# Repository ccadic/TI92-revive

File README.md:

# TI92-revive
Reviing the TI92 calculator with a new KICAD PCB and a new 4 inch display

This project is still experimental. We need you help !!!!

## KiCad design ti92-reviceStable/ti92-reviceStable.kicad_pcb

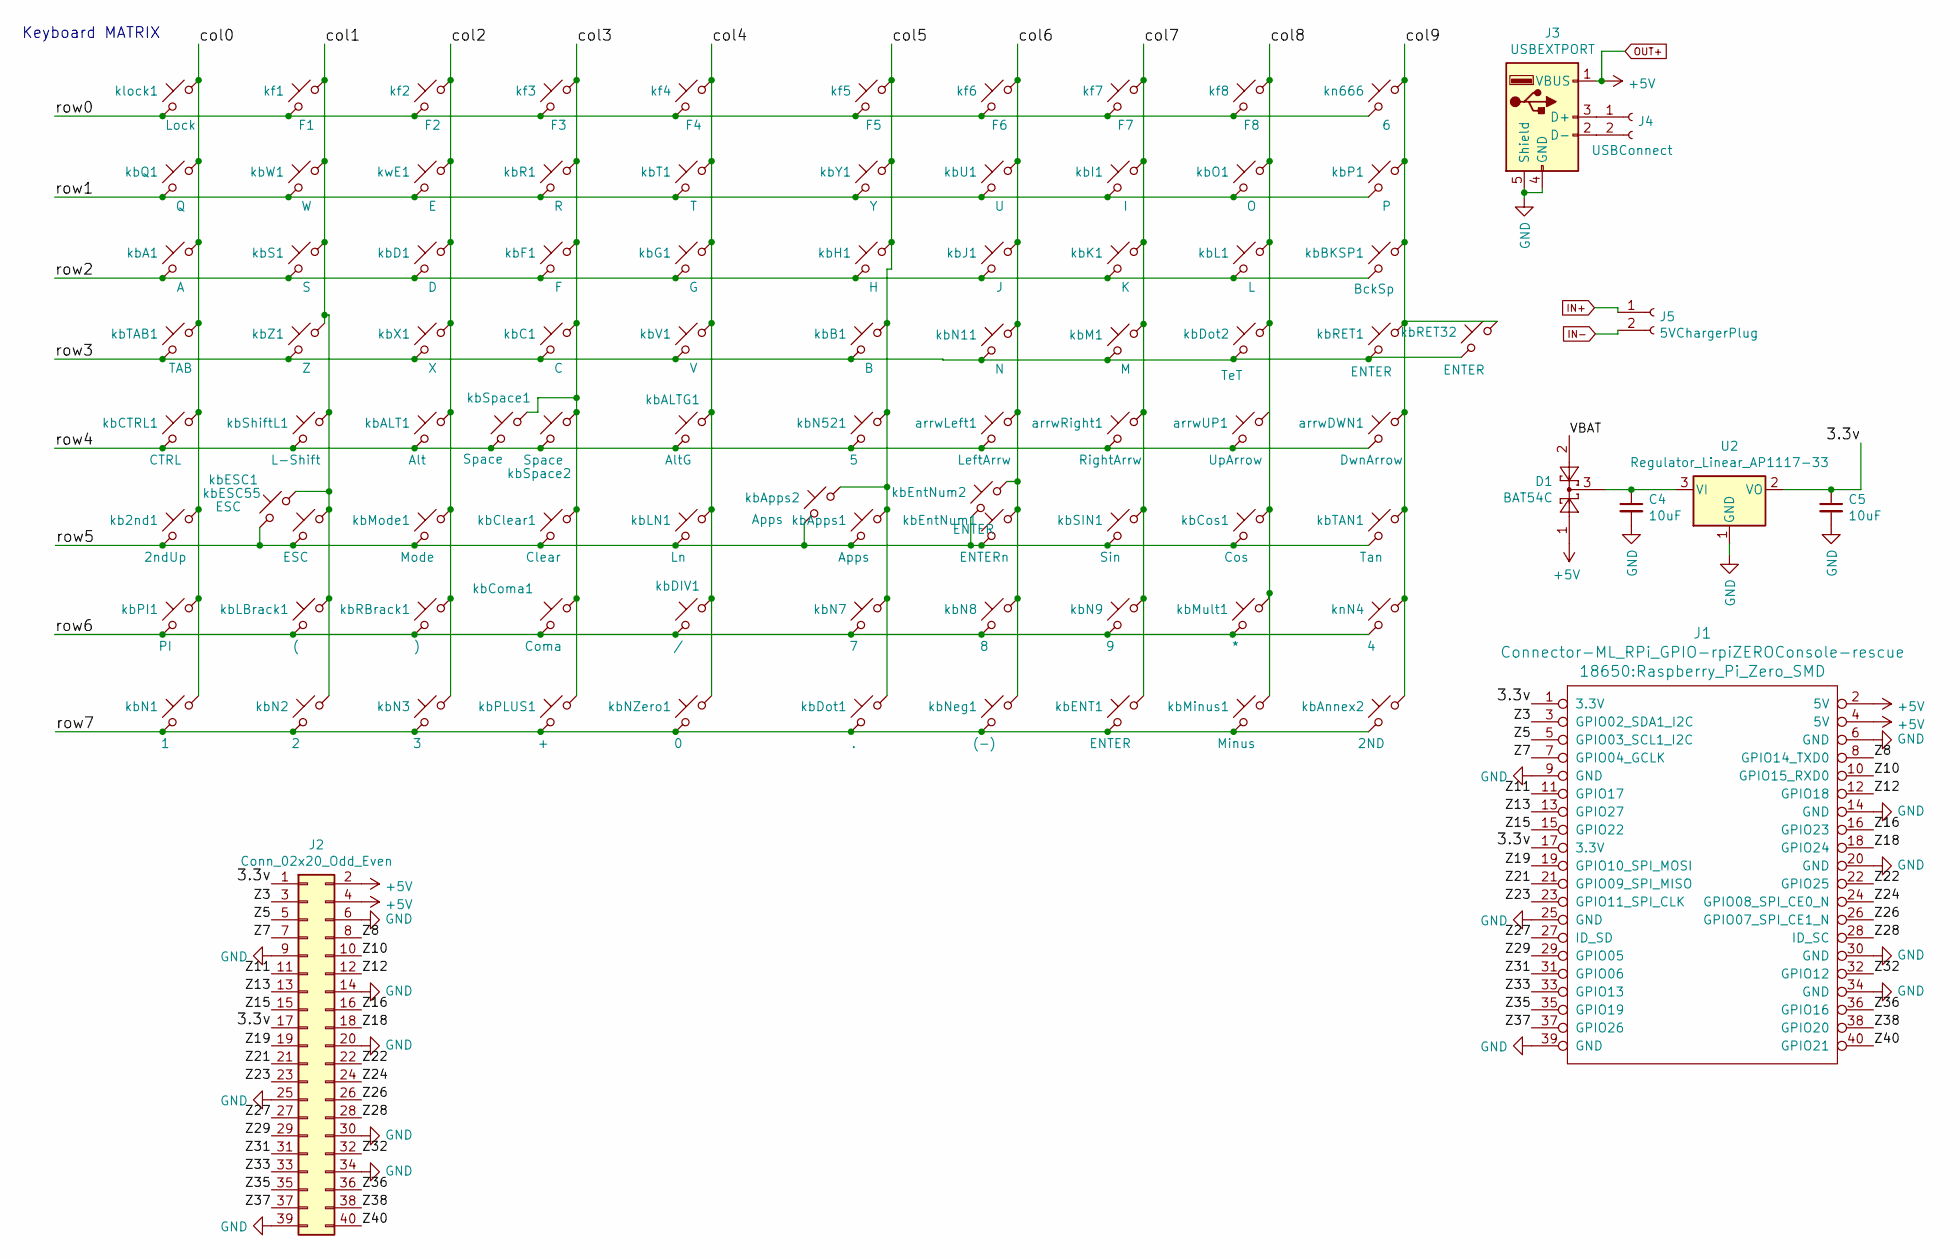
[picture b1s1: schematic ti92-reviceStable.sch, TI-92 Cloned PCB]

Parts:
C4, C5: 10uF; C_0805_2012Metric_Pad1.18x1.45mm_HandSolder
D1: BAT54C; SOT-23
J1: Connector-ML_RPi_GPIO-rpiZEROConsole-rescue; Raspberry_Pi_Zero_SMD
J2: Conn_02x20_Odd_Even; 4inchIPSDisplay
J3: USBEXTPORT; usbAsmd
J4: USBConnect; 2pads
J5: 5VChargerPlug; BARREL_JACK
U2: Regulator_Linear_AP1117-33; SOT-223-3_TabPin2
arrwDWN1: DwnArrow; Kpad6
arrwLeft1: LeftArrw; Kpad6
arrwRight1: RightArrw; Kpad6
arrwUP1: UpArrow; Kpad6
kb2nd1: 2ndUp; Kpad6
kbA1: A; Kpad6
kbALT1: Alt; Kpad6
kbALTG1: AltG; Kpad6
kbAnnex2: 2ND; Kpad6
kbApps1, kbApps2: Apps; Kpad6
kbB1: B; Kpad6
kbBKSP1: BckSp; Kpad6
kbC1: C; Kpad6
kbCTRL1: CTRL; Kpad6
kbClear1: Clear; Kpad6
kbComa1: Coma; Kpad6
kbCos1: Cos; Kpad6
kbD1: D; Kpad6
kbDIV1: /; Kpad6
kbDot1: .; Kpad6
kbDot2: TeT; Kpad6
kbENT1: ENTER; Kpad6
kbESC1, kbESC55: ESC; Kpad6
kbEntNum1: ENTERn; Kpad6
kbEntNum2: ENTER; Kpad6
kbF1: F; Kpad6
kbG1: G; Kpad6
kbH1: H; Kpad6
kbI1: I; Kpad6
kbJ1: J; Kpad6
kbK1: K; Kpad6
kbL1: L; Kpad6
kbLBrack1: (; Kpad6
kbLN1: Ln; Kpad6
kbM1: M; Kpad6
kbMinus1: Minus; Kpad6
kbMode1: Mode; Kpad6
kbMult1: *; Kpad6
kbN1: 1; Kpad6
kbN2: 2; Kpad6
kbN3: 3; Kpad6
kbN7: 7; Kpad6
kbN8: 8; Kpad6
kbN9: 9; Kpad6
kbN11: N; Kpad6
kbN521: 5; Kpad6
kbNZero1: 0; Kpad6
kbNeg1: (-); Kpad6
kbO1: O; Kpad6
kbP1: P; Kpad6
kbPI1: PI; Kpad6
kbPLUS1: +; Kpad6
kbQ1: Q; Kpad6
kbR1: R; Kpad6
kbRBrack1: ); Kpad6
kbRET1, kbRET32: ENTER; Kpad6
kbS1: S; Kpad6
kbSIN1: Sin; Kpad6
kbShiftL1: L-Shift; Kpad6
kbSpace1, kbSpace2: Space; Kpad6
kbT1: T; Kpad6
kbTAB1: TAB; Kpad6
kbTAN1: Tan; Kpad6
kbU1: U; Kpad6
kbV1: V; Kpad6
kbW1: W; Kpad6
kbX1: X; Kpad6
kbY1: Y; Kpad6
kbZ1: Z; Kpad6
kf1: F1; Kpad6
kf2: F2; Kpad6
kf3: F3; Kpad6
kf4: F4; Kpad6
kf5: F5; Kpad6
kf6: F6; Kpad6
kf7: F7; Kpad6
kf8: F8; Kpad6
klock1: Lock; Kpad6
kn666: 6; Kpad6
knN4: 4; Kpad6
kwE1: E; Kpad6

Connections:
/3.3v: C5.1, J1.1 (3.3V), J1.17 (3.3V), J2.1, J2.17, U2.2 (VO)
/VBAT: D1.2
/Z3: J1.3 (GPIO02_SDA1_I2C), J2.3
/Z5: J1.5 (GPIO03_SCL1_I2C), J2.5
/Z7: J1.7 (GPIO04_GCLK), J2.7
/Z8: J1.8 (GPIO14_TXD0), J2.8
/Z10: J1.10 (GPIO15_RXD0), J2.10
/Z11: J1.11 (GPIO17), J2.11
/Z12: J1.12 (GPIO18), J2.12
/Z13: J1.13 (GPIO27), J2.13
/Z15: J1.15 (GPIO22), J2.15
/Z16: J1.16 (GPIO23), J2.16
/Z18: J1.18 (GPIO24), J2.18
/Z19: J1.19 (GPIO10_SPI_MOSI), J2.19
/Z21: J1.21 (GPIO09_SPI_MISO), J2.21
/Z22: J1.22 (GPIO25), J2.22
/Z23: J1.23 (GPIO11_SPI_CLK), J2.23
/Z24: J1.24 (GPIO08_SPI_CE0_N), J2.24
/Z26: J1.26 (GPIO07_SPI_CE1_N), J2.26
/Z27: J1.27 (ID_SD), J2.27
/Z28: J1.28 (ID_SC), J2.28
/Z29: J1.29 (GPIO05), J2.29
/Z31: J1.31 (GPIO06), J2.31
/Z32: J1.32 (GPIO12), J2.32
/Z33: J1.33 (GPIO13), J2.33
/Z35: J1.35 (GPIO19), J2.35
/Z36: J1.36 (GPIO16), J2.36
/Z37: J1.37 (GPIO26), J2.37
/Z38: J1.38 (GPIO20), J2.38
/Z40: J1.40 (GPIO21), J2.40
/col0: kb2nd1.1, kbA1.1, kbCTRL1.1, kbN1.1, kbPI1.1, kbQ1.1, kbTAB1.1, klock1.1
/col1: kbESC1.1, kbESC55.1, kbLBrack1.1, kbN2.1, kbS1.1, kbShiftL1.1, kbW1.1, kbZ1.1, kf1.1
/col2: kbALT1.1, kbD1.1, kbMode1.1, kbN3.1, kbRBrack1.1, kbX1.1, kf2.1, kwE1.1
/col3: kbC1.1, kbClear1.1, kbComa1.1, kbF1.1, kbPLUS1.1, kbR1.1, kbSpace1.1, kbSpace2.1, kf3.1
/col4: kbALTG1.1, kbDIV1.1, kbG1.1, kbLN1.1, kbNZero1.1, kbT1.1, kbV1.1, kf4.1
/col5: kbApps1.1, kbApps2.1, kbB1.1, kbDot1.1, kbH1.1, kbN7.1, kbN521.1, kbY1.1, kf5.1
/col6: arrwLeft1.1, kbEntNum1.1, kbEntNum2.1, kbJ1.1, kbN8.1, kbN11.1, kbNeg1.1, kbU1.1, kf6.1
/col7: arrwRight1.1, kbENT1.1, kbI1.1, kbK1.1, kbM1.1, kbN9.1, kbSIN1.1, kf7.1
/col8: kbCos1.1, kbDot2.1, kbL1.1, kbMinus1.1, kbMult1.1, kbO1.1, kf8.1
/col9: arrwDWN1.1, kbAnnex2.1, kbBKSP1.1, kbP1.1, kbRET1.1, kbRET32.1, kbTAN1.1, kn666.1, knN4.1
/row0: kf1.2, kf2.2, kf3.2, kf4.2, kf5.2, kf6.2, kf7.2, kf8.2, klock1.2, kn666.2
/row1: kbI1.2, kbO1.2, kbP1.2, kbQ1.2, kbR1.2, kbT1.2, kbU1.2, kbW1.2, kbY1.2, kwE1.2
/row2: kbA1.2, kbBKSP1.2, kbD1.2, kbF1.2, kbG1.2, kbH1.2, kbJ1.2, kbK1.2, kbL1.2, kbS1.2
/row3: kbB1.2, kbC1.2, kbDot2.2, kbM1.2, kbN11.2, kbRET1.2, kbRET32.2, kbTAB1.2, kbV1.2, kbX1.2, kbZ1.2
/row4: arrwDWN1.2, arrwLeft1.2, arrwRight1.2, arrwUP1.2, kbALT1.2, kbALTG1.2, kbCTRL1.2, kbN521.2, kbShiftL1.2, kbSpace1.2, kbSpace2.2
/row5: kb2nd1.2, kbApps1.2, kbApps2.2, kbClear1.2, kbCos1.2, kbESC1.2, kbESC55.2, kbEntNum1.2, kbEntNum2.2, kbLN1.2, kbMode1.2, kbSIN1.2, kbTAN1.2
/row6: kbComa1.2, kbDIV1.2, kbLBrack1.2, kbMult1.2, kbN7.2, kbN8.2, kbN9.2, kbPI1.2, kbRBrack1.2, knN4.2
/row7: kbAnnex2.2, kbDot1.2, kbENT1.2, kbMinus1.2, kbN1.2, kbN2.2, kbN3.2, kbNZero1.2, kbNeg1.2, kbPLUS1.2
GND: C4.2, C5.2, J1.6 (GND), J1.9 (GND), J1.14 (GND), J1.20 (GND), J1.25 (GND), J1.30 (GND), J1.34 (GND), J1.39 (GND), J2.6, J2.9, J2.14, J2.20, J2.25, J2.30, J2.34, J2.39, J3.4 (GND), J3.5 (Shield), U2.1 (GND)
IN+: J5.1
IN-: J5.2
unnamed: C4.1, D1.3, U2.3 (VI)
unnamed: J3.2 (D-), J4.2
unnamed: J3.3 (D+), J4.1
OUT+: D1.1, J1.2 (5V), J1.4 (5V), J2.2, J2.4, J3.1 (VBUS)

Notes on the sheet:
Keyboard MATRIX

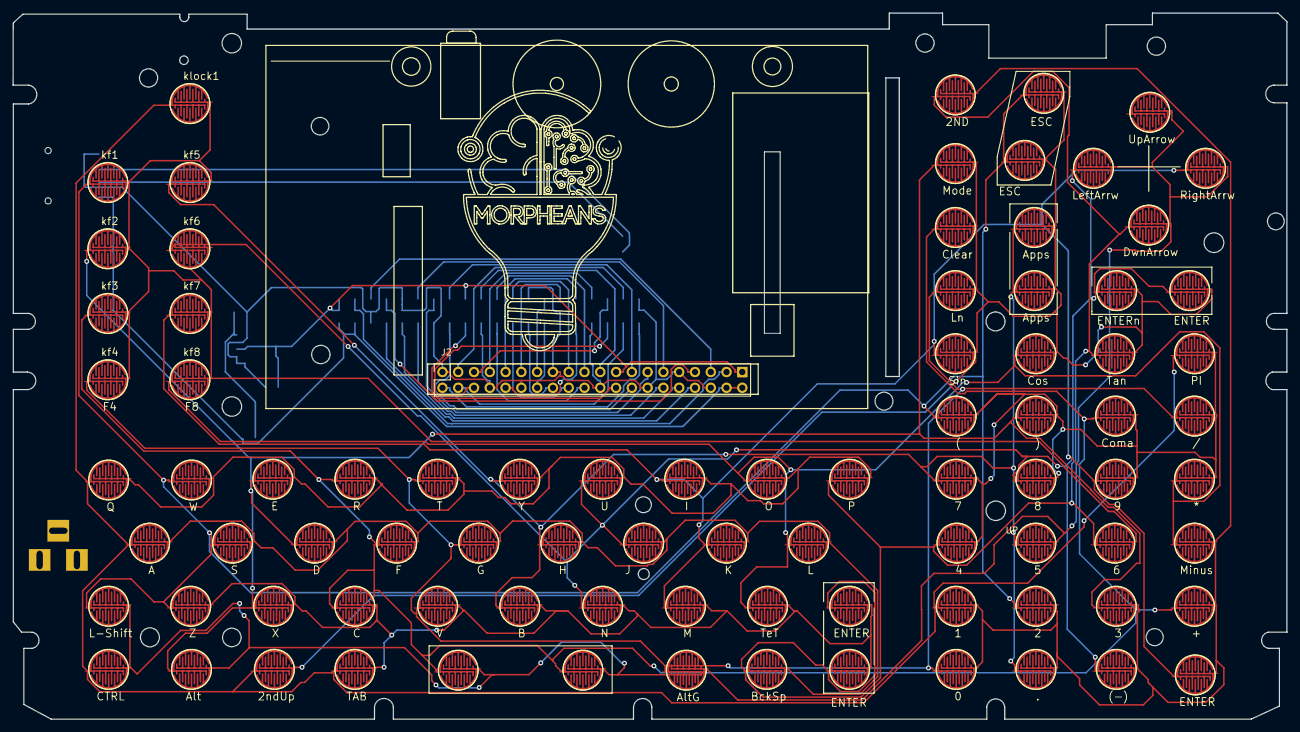
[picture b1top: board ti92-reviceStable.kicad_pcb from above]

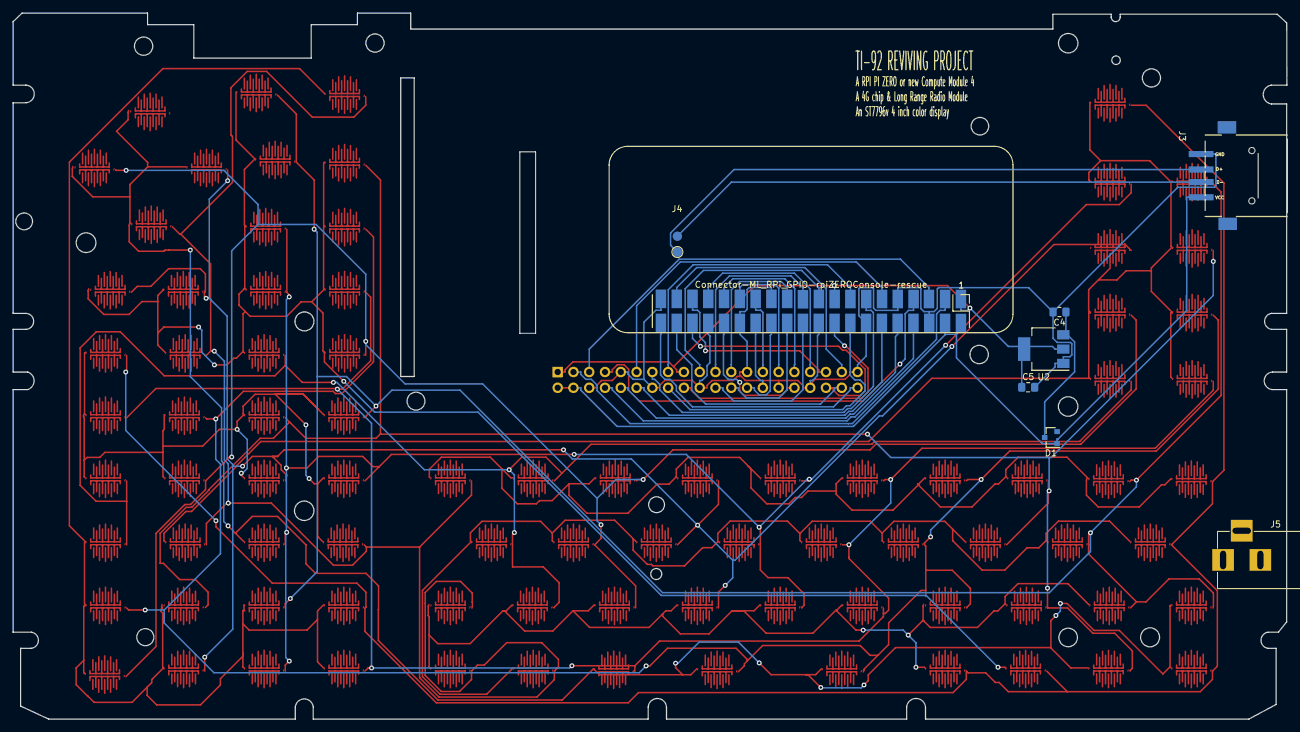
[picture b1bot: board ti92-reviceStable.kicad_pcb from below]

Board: 2 copper layers, 205.0 x 113.6 mm, 94 parts (8 on the bottom side), 52 nets.

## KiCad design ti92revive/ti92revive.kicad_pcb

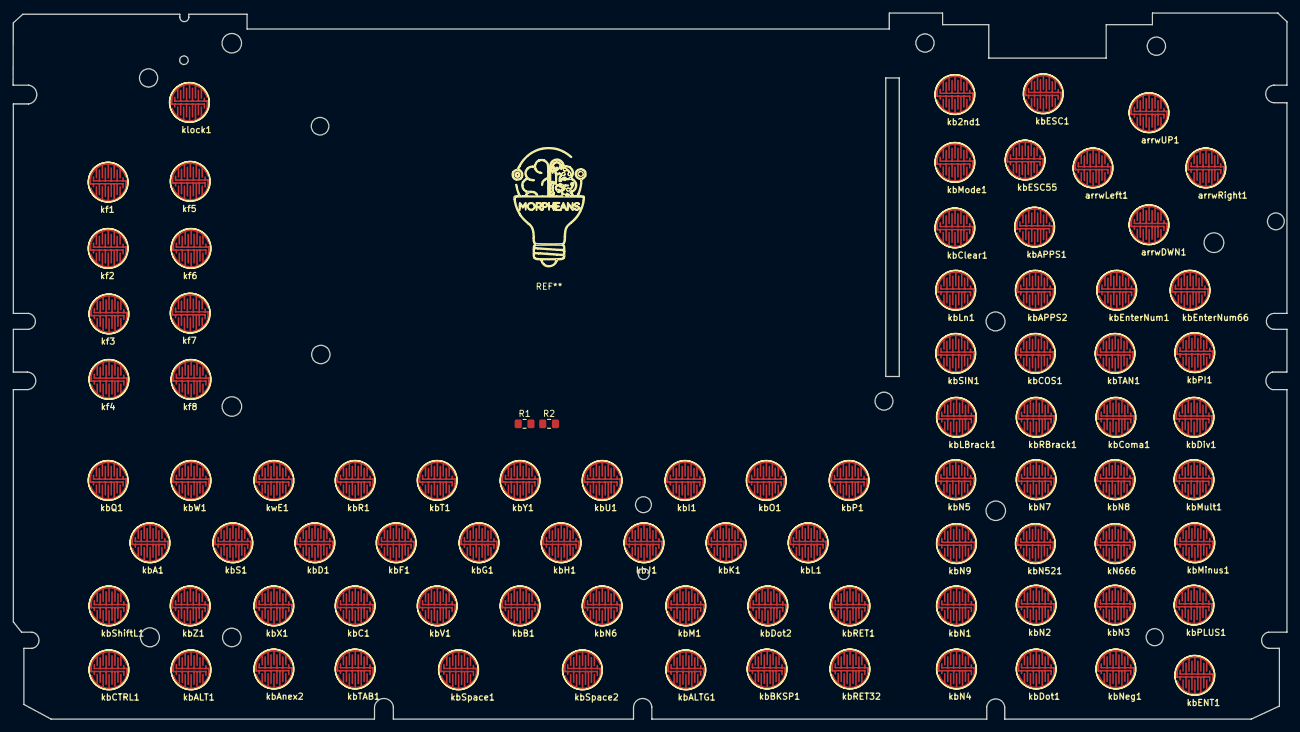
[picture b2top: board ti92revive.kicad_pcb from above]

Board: 2 copper layers, 205.0 x 113.6 mm, 88 parts (1 on the bottom side), 21 nets, no tracks yet.

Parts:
IC1: TCA8418; TCA8418-WQFN-24-1EP_4x4mm
R1: 4.7k; R_0805_2012Metric_Pad1.15x1.40mm_HandSolder
R2: 10k; R_0805_2012Metric_Pad1.15x1.40mm_HandSolder
arrwDWN1: ArwDwn; Kbpad
arrwLeft1: ArwLeft; Kbpad
arrwRight1: ArwRight; Kbpad
arrwUP1: ArwUP; Kbpad
kN666: 6; Kbpad
kb2nd1: 2ndUP; Kbpad
kbA1: A; Kbpad
kbALT1: Alt; Kbpad
kbALTG1: AltG; Kbpad
kbAPPS1, kbAPPS2: Apps; Kbpad
kbAnex2: BTN2; Kbpad
kbB1: B; Kbpad
kbBKSP1: BckSp; Kbpad
kbC1: C; Kbpad
kbCOS1: Cos; Kbpad
kbCTRL1: CTRL; Kbpad
kbClear1: Clear; Kbpad
kbComa1: Coma; Kbpad
kbD1: D; Kbpad
kbDiv1: /; Kbpad
kbDot1: .; Kbpad
kbDot2: Tet; Kbpad
kbENT1: ENTER; Kbpad
kbESC1, kbESC55: ESC; Kbpad
kbEnterNum1, kbEnterNum66: EnterN; Kbpad
kbF1: F; Kbpad
kbG1: G; Kbpad
kbH1: H; Kbpad
kbI1: I; Kbpad
kbJ1: J; Kbpad
kbK1: K; Kbpad
kbL1: L; Kbpad
kbLBrack1: (; Kbpad
kbLn1: LN; Kbpad
kbM1: M; Kbpad
kbMinus1: Minus; Kbpad
kbMode1: Mode; Kbpad
kbMult1: *; Kbpad
kbN1: 1; Kbpad
kbN2: 2; Kbpad
kbN3: 3; Kbpad
kbN4: 0; Kbpad
kbN5: 7; Kbpad
kbN6: N; Kbpad
kbN7: 8; Kbpad
kbN8: 9; Kbpad
kbN9: 4; Kbpad
kbN521: 5; Kbpad
kbNeg1: (-); Kbpad
kbO1: O; Kbpad
kbP1: P; Kbpad
kbPI1: PI; Kbpad
kbPLUS1: +; Kbpad
kbQ1: Q; Kbpad
kbR1: R; Kbpad
kbRBrack1: ); Kbpad
kbRET1, kbRET32: Return; Kbpad
kbS1: S; Kbpad
kbSIN1: Sin; Kbpad
kbShiftL1: L-Shift; Kbpad
kbSpace1, kbSpace2: Space; Kbpad
kbT1: T; Kbpad
kbTAB1: TAB; Kbpad
kbTAN1: Tan; Kbpad
kbU1: U; Kbpad
kbV1: V; Kbpad
kbW1: W; Kbpad
kbX1: X; Kbpad
kbY1: Y; Kbpad
kbZ1: Z; Kbpad
kf1: F1; Kbpad
kf2: F2; Kbpad
kf3: F3; Kbpad
kf4: F4; Kbpad
kf5: F5; Kbpad
kf6: F6; Kbpad
kf7: F7; Kbpad
kf8: F8; Kbpad
klock1: lock; Kbpad
kwE1: E; Kbpad

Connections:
/3.3v: IC1.21 (VCC), R1.2, R2.1
/col0: IC1.9 (Col0), kb2nd1.1, kbA1.1, kbCTRL1.1, kbN1.1, kbPI1.1, kbQ1.1, kbTAB1.1, klock1.1
/col1: IC1.10 (Col1), kbESC1.1, kbESC55.1, kbLBrack1.1, kbN2.1, kbS1.1, kbShiftL1.1, kbW1.1, kbZ1.1, kf1.1
/col2: IC1.11 (Col2), kbALT1.1, kbD1.1, kbMode1.1, kbN3.1, kbRBrack1.1, kbX1.1, kf2.1, kwE1.1
/col3: IC1.12 (Col3), kbC1.1, kbClear1.1, kbComa1.1, kbF1.1, kbPLUS1.1, kbR1.1, kbSpace1.1, kbSpace2.1, kf3.1
/col4: IC1.13 (Col4), kbALTG1.1, kbDiv1.1, kbG1.1, kbLn1.1, kbN4.1, kbT1.1, kbV1.1, kf4.1
/col5: IC1.14 (Col5), kbAPPS1.1, kbAPPS2.1, kbB1.1, kbDot1.1, kbH1.1, kbN5.1, kbN521.1, kbY1.1, kf5.1
/col6: IC1.15 (Col6), arrwLeft1.1, kbEnterNum1.1, kbEnterNum66.1, kbJ1.1, kbN6.1, kbN7.1, kbNeg1.1, kbU1.1, kf6.1
/col7: IC1.16 (Col7), arrwRight1.1, kbENT1.1, kbI1.1, kbK1.1, kbM1.1, kbN8.1, kbSIN1.1, kf7.1
/col8: IC1.17 (Col8), kbCOS1.1, kbDot2.1, kbL1.1, kbMinus1.1, kbMult1.1, kbO1.1, kf8.1
/col9: IC1.18 (Col9), arrwDWN1.1, kN666.1, kbAnex2.1, kbBKSP1.1, kbN9.1, kbP1.1, kbRET1.1, kbRET32.1, kbTAN1.1
/row0: IC1.8 (Row0), kN666.2, kf1.2, kf2.2, kf3.2, kf4.2, kf5.2, kf6.2, kf7.2, kf8.2, klock1.2
/row1: IC1.7 (Row1), kbI1.2, kbO1.2, kbP1.2, kbQ1.2, kbR1.2, kbT1.2, kbU1.2, kbW1.2, kbY1.2, kwE1.2
/row2: IC1.6 (Row2), kbA1.2, kbBKSP1.2, kbD1.2, kbF1.2, kbG1.2, kbH1.2, kbJ1.2, kbK1.2, kbL1.2, kbS1.2
/row3: IC1.5 (Row3), kbB1.2, kbC1.2, kbDot2.2, kbM1.2, kbN6.2, kbRET1.2, kbRET32.2, kbTAB1.2, kbV1.2, kbX1.2, kbZ1.2
/row4: IC1.4 (Row4), arrwDWN1.2, arrwLeft1.2, arrwRight1.2, arrwUP1.2, kbALT1.2, kbALTG1.2, kbCTRL1.2, kbN521.2, kbShiftL1.2, kbSpace1.2, kbSpace2.2
/row5: IC1.3 (Row5), kb2nd1.2, kbAPPS1.2, kbAPPS2.2, kbCOS1.2, kbClear1.2, kbESC1.2, kbESC55.2, kbEnterNum1.2, kbEnterNum66.2, kbLn1.2, kbMode1.2, kbSIN1.2, kbTAN1.2
/row6: IC1.2 (Row6), kbComa1.2, kbDiv1.2, kbLBrack1.2, kbMult1.2, kbN5.2, kbN7.2, kbN8.2, kbN9.2, kbPI1.2, kbRBrack1.2
/row7: IC1.1 (Row7), kbAnex2.2, kbDot1.2, kbENT1.2, kbMinus1.2, kbN1.2, kbN2.2, kbN3.2, kbN4.2, kbNeg1.2, kbPLUS1.2
INT: IC1.24 (INT), R1.1
unnamed: IC1.20 (RESET), R2.2
